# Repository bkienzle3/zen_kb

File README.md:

# zen_kb

"Maximalist" ergo mech split keyboard. 38-keys, 3 rotary encoders, 1 trackpad. My last keyboard was mu (無), meaning nothing. Since this adds a lot of extra bells and whistles, I've named it zen (全), meaning all. This keyboard is meant to be much more "finished" than mu. With that said, this is still an eternal work in progress. The hardware is finished, at least. The config is a never ending journey.

## Firmware
Firmware is located in qmk_firmware. Keymaps are based on Miryoku (manna-harbour/miryoku), with my own customizations, of course.

## Bill of materials

Kailh Choc V1 key switches x 38
<br>KB2040 x 2 (MCU - runs on 3.3v, important for trackpad)
<br>1N4148 MiniMELF diode x 38
<br>TRRS-PJ-320A x 2 (TRRS jacks)
<br>Alps EC12E2440301 x 2 (Mini encoders)
<br>Alps EC12E24404A8 x 1 (Jog wheel encoder)
<br>Cirque TM040040-2024-303 x 1 (trackpad)
<br>Molex 505110-1297 x 1
<br>.50 mm pitch type B FFC x 1
<br>M2*6mm screws, hex socket head x 12
<br>M2 heat set inserts x 12

## Other
I recommend putting some sort of grip tape around the knobs. I'm using self-fusing silicone tape, but anything should work.

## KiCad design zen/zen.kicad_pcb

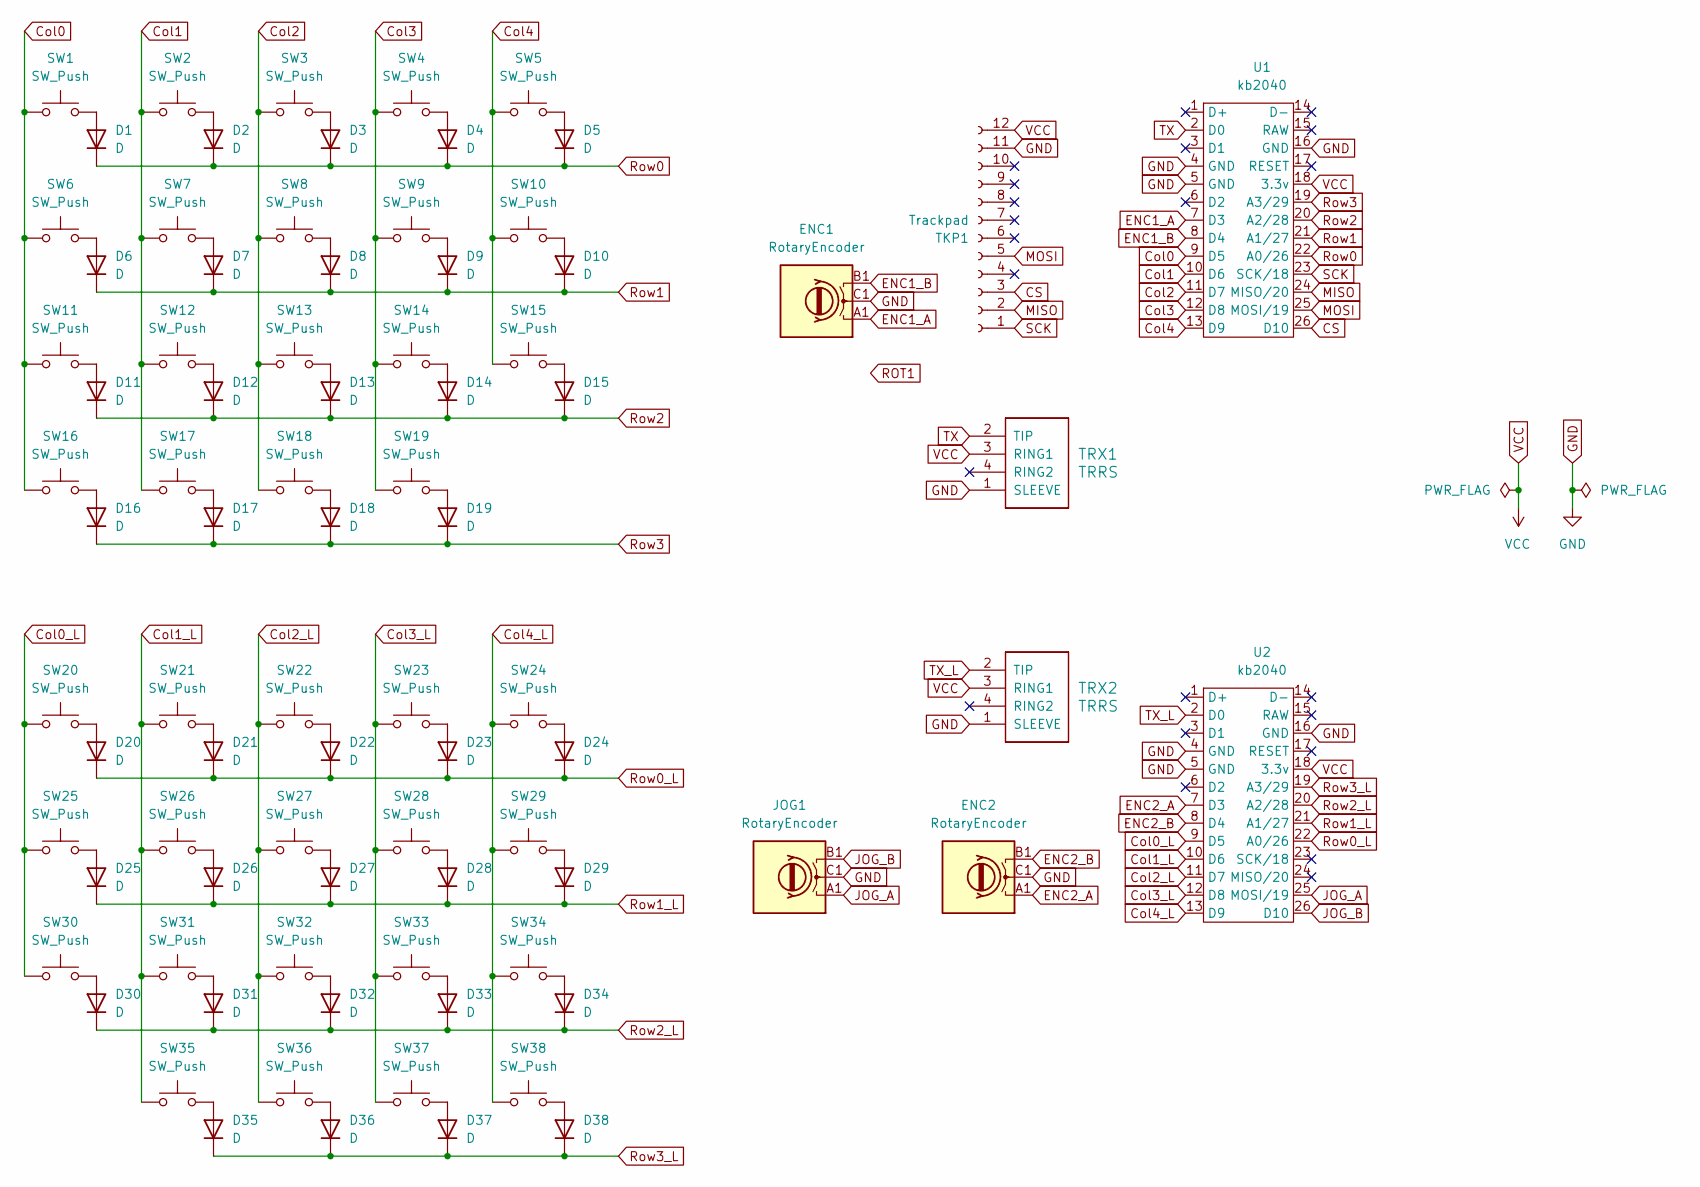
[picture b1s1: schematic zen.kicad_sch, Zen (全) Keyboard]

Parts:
D1, D2, D3, D4, D5, D6, D7, D8, D9, D10, D11, D12, D13, D14, D15, D16, D17, D18, D19, D20, D21, D22, D23, D24, D25, D26, D27, D28, D29, D30, D31, D32, D33, D34, D35, D36, D37, D38: D; D_MiniMELF
ENC1, ENC2: RotaryEncoder; EC12E2440301
JOG1: RotaryEncoder; EC12E2440301
SW1, SW2, SW3, SW4, SW5, SW6, SW7, SW8, SW9, SW10, SW11, SW12, SW13, SW14, SW15, SW16, SW17, SW18, SW19, SW20, SW21, SW22, SW23, SW24, SW25, SW26, SW27, SW28, SW29, SW30, SW31, SW32, SW33, SW34, SW35, SW36, SW37, SW38: SW_Push; SW_PG1350
TKP1: Trackpad; 5051101297
TRX1, TRX2: TRRS; TRRS-PJ-320A
U1, U2: kb2040

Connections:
CS: TKP1.3, U1.26 (D10)
Col0: SW1.1, SW6.1, SW11.1, SW16.1, U1.9 (D5)
Col0_L: SW20.1, SW25.1, SW30.1, U2.9 (D5)
Col1: SW2.1, SW7.1, SW12.1, SW17.1, U1.10 (D6)
Col1_L: SW21.1, SW26.1, SW31.1, SW35.1, U2.10 (D6)
Col2: SW3.1, SW8.1, SW13.1, SW18.1, U1.11 (D7)
Col2_L: SW22.1, SW27.1, SW32.1, SW36.1, U2.11 (D7)
Col3: SW4.1, SW9.1, SW14.1, SW19.1, U1.12 (D8)
Col3_L: SW23.1, SW28.1, SW33.1, SW37.1, U2.12 (D8)
Col4: SW5.1, SW10.1, SW15.1, U1.13 (D9)
Col4_L: SW24.1, SW29.1, SW34.1, SW38.1, U2.13 (D9)
ENC1_A: ENC1.A1, U1.7 (D3)
ENC1_B: ENC1.B1, U1.8 (D4)
ENC2_A: ENC2.A1, U2.7 (D3)
ENC2_B: ENC2.B1, U2.8 (D4)
GND: ENC1.C1, ENC2.C1, JOG1.C1, TKP1.11, TRX1.1 (SLEEVE), TRX2.1 (SLEEVE), U1.4 (GND), U1.5 (GND), U1.16 (GND), U2.4 (GND), U2.5 (GND), U2.16 (GND)
JOG_A: JOG1.A1, U2.25 (MOSI/19)
JOG_B: JOG1.B1, U2.26 (D10)
MISO: TKP1.2, U1.24 (MISO/20)
MOSI: TKP1.5, U1.25 (MOSI/19)
unnamed: D1.2 (A), SW1.2
unnamed: D2.2 (A), SW2.2
unnamed: D3.2 (A), SW3.2
unnamed: D4.2 (A), SW4.2
unnamed: D5.2 (A), SW5.2
unnamed: D6.2 (A), SW6.2
unnamed: D7.2 (A), SW7.2
unnamed: D8.2 (A), SW8.2
unnamed: D9.2 (A), SW9.2
unnamed: D10.2 (A), SW10.2
unnamed: D11.2 (A), SW11.2
unnamed: D12.2 (A), SW12.2
unnamed: D13.2 (A), SW13.2
unnamed: D14.2 (A), SW14.2
unnamed: D15.2 (A), SW15.2
unnamed: D16.2 (A), SW16.2
unnamed: D17.2 (A), SW17.2
unnamed: D18.2 (A), SW18.2
unnamed: D19.2 (A), SW19.2
unnamed: D20.2 (A), SW20.2
unnamed: D21.2 (A), SW21.2
unnamed: D22.2 (A), SW22.2
unnamed: D23.2 (A), SW23.2
unnamed: D24.2 (A), SW24.2
unnamed: D25.2 (A), SW25.2
unnamed: D26.2 (A), SW26.2
unnamed: D27.2 (A), SW27.2
unnamed: D28.2 (A), SW28.2
unnamed: D29.2 (A), SW29.2
unnamed: D30.2 (A), SW30.2
unnamed: D31.2 (A), SW31.2
unnamed: D32.2 (A), SW32.2
unnamed: D33.2 (A), SW33.2
unnamed: D34.2 (A), SW34.2
unnamed: D35.2 (A), SW35.2
unnamed: D36.2 (A), SW36.2
unnamed: D37.2 (A), SW37.2
unnamed: D38.2 (A), SW38.2
Row0: D1.1 (K), D2.1 (K), D3.1 (K), D4.1 (K), D5.1 (K), U1.22 (A0/26)
Row0_L: D20.1 (K), D21.1 (K), D22.1 (K), D23.1 (K), D24.1 (K), U2.22 (A0/26)
Row1: D6.1 (K), D7.1 (K), D8.1 (K), D9.1 (K), D10.1 (K), U1.21 (A1/27)
Row1_L: D25.1 (K), D26.1 (K), D27.1 (K), D28.1 (K), D29.1 (K), U2.21 (A1/27)
Row2: D11.1 (K), D12.1 (K), D13.1 (K), D14.1 (K), D15.1 (K), U1.20 (A2/28)
Row2_L: D30.1 (K), D31.1 (K), D32.1 (K), D33.1 (K), D34.1 (K), U2.20 (A2/28)
Row3: D16.1 (K), D17.1 (K), D18.1 (K), D19.1 (K), U1.19 (A3/29)
Row3_L: D35.1 (K), D36.1 (K), D37.1 (K), D38.1 (K), U2.19 (A3/29)
SCK: TKP1.1, U1.23 (SCK/18)
TX: TRX1.2 (TIP), U1.2 (D0)
TX_L: TRX2.2 (TIP), U2.2 (D0)
VCC: TKP1.12, TRX1.3 (RING1), TRX2.3 (RING1), U1.18 (3.3v), U2.18 (3.3v)

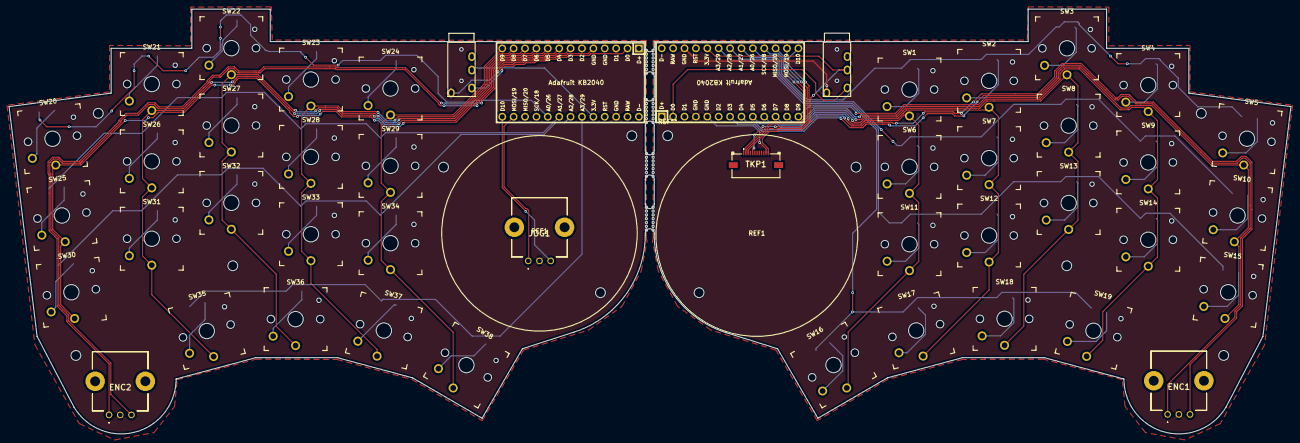
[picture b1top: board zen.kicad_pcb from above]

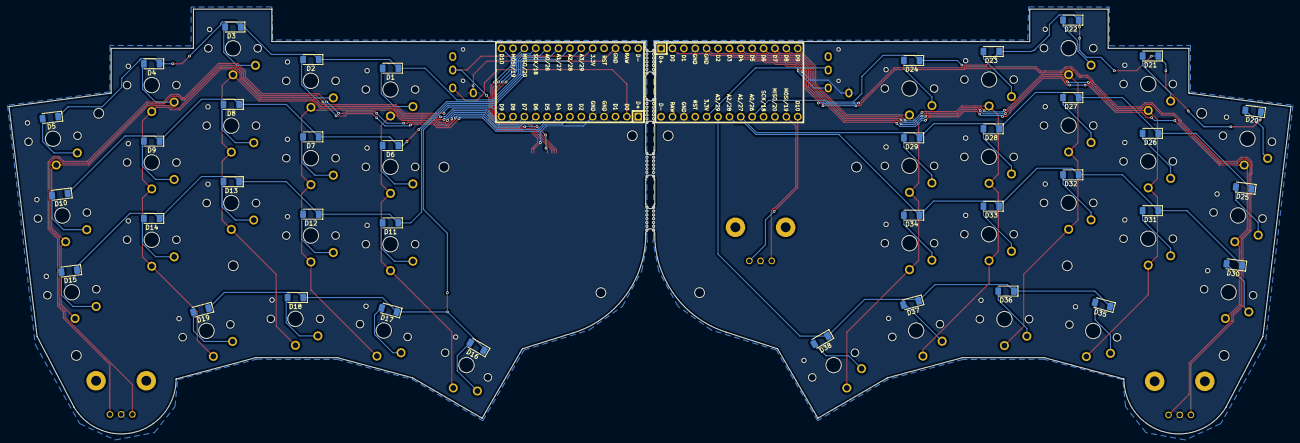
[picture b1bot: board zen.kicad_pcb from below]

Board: 2 copper layers, 285.9 x 94.7 mm, 86 parts (38 on the bottom side), 70 nets.

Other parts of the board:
REF1, REF1#2: Cirque Curved Trackpad; Cirque Curved 40mm Trackpad

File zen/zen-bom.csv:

"Id";"Designator";"Footprint";"Quantity";"Designation";"Supplier and ref";
1;",,,,,,,,,,";"";11;"";;;
2;"SW22,SW23,SW18,SW26,SW38,SW33,SW11,SW19,SW30,SW37,SW17,SW5,SW24,SW2,SW7,SW6,SW32,SW13,SW27,SW4,SW12,SW16,SW34,SW1,SW3,SW14,SW29,SW25,SW31,SW28,SW21,SW9,SW36,SW35,SW20,SW15,SW10,SW8";"SW_PG1350";38;"SW_Push";;;
3;"U1,U2";"kb2040";2;"kb2040";;;
4;"TRX2,TRX1";"TRRS-PJ-320A";2;"TRRS";;;
5;"ENC2,JOG1,ENC1";"EC12E2440301";3;"RotaryEncoder";;;
6;"REF1,REF1";"Cirque Curved 40mm Trackpad";2;"Cirque Curved Trackpad";;;
7;"TKP1";"5051101297";1;"Trackpad";;;
8;"D33,D15,D14,D6,D38,D2,D31,D9,D22,D13,D26,D17,D24,D12,D36,D1,D16,D11,D28,D29,D7,D35,D8,D10,D20,D37,D23,D21,D32,D18,D3,D19,D25,D5,D27,D30,D4,D34";"D_MiniMELF";38;"D";;;

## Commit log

2025-09-01 initial commit, pcb design well underway
2025-09-01 add gitignore
2025-10-04 pcb complete
2025-10-04 add 3d printed parts
2025-10-04 add firmware
